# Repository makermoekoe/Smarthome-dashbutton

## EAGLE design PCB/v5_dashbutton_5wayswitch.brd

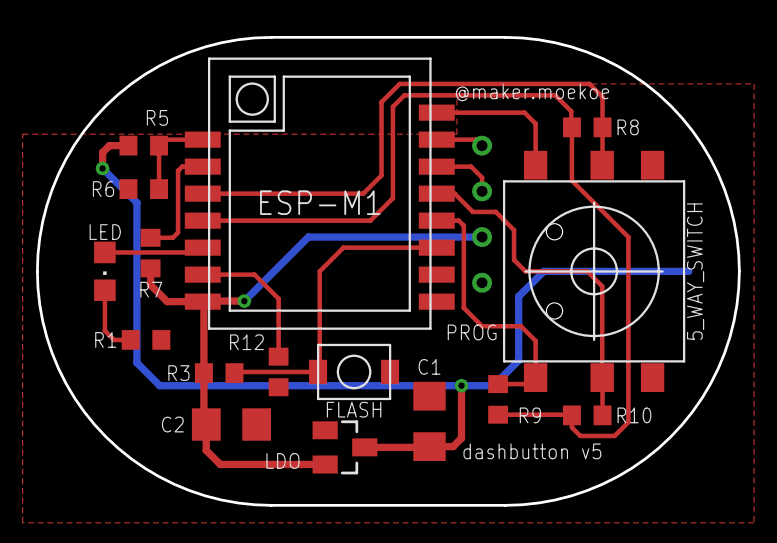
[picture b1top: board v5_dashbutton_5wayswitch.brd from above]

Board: 2 copper layers, 39.0 x 26.0 mm, 18 parts (1 on the bottom side), 16 nets.

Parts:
5_WAY_SWITCH: 5WAY_TACTILE_SWITCH
C1, C2: 1u; C1206
FLASH: 3X4_SMD_BUTTON; 3X4BUTTON
LDO: MCP1700; SOT23
LED: CHIPLED_0805
PROG: PROG_CON
R1: 1k; R0603
R3, R6, R7, R8, R9, R10, R12: 100k; R0603
R5: 330k; R0603
U$2: 2450_BATTERYHOLDER_SMD
U$3: ESP8285-M1

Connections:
4_5WAY_DOWN: 5_WAY_SWITCH.P6, R9.1, U$3.GPIO4
5_5WAY_RIGHT: 5_WAY_SWITCH.P5, R10.1, U$3.GPIO5
12_5WAY_HIGH: R8.1, R9.2, R10.2, U$3.GPIO12
14_5WAY_LEFT: 5_WAY_SWITCH.P2, R8.2, U$3.GPIO14
ADC: R5.2, R6.1, U$3.ADC
GND: 5_WAY_SWITCH.P1, C1.2, C2.2, FLASH.P$2, LDO.1, PROG.GND, R1.2, R6.2, R12.1, U$2.GND, U$3.GND
GPIO0_PROG: FLASH.P$1, R3.2, U$3.GPIO0
GPIO1: R12.2, U$3.GPIO15
GPIO13_LED: LED.A, U$3.GPIO13
unnamed: R7.2, U$3.EN
unnamed: LED.C, R1.1
RESET: 5_WAY_SWITCH.P3, U$3.RST
RXD: PROG.RXD, U$3.RXD
TXD: PROG.TXD, U$3.TXD
V33: C2.1, LDO.2, PROG.VCC, R3.1, R7.1, U$3.V33
VCC: C1.1, LDO.3, R5.1, U$2.VCC

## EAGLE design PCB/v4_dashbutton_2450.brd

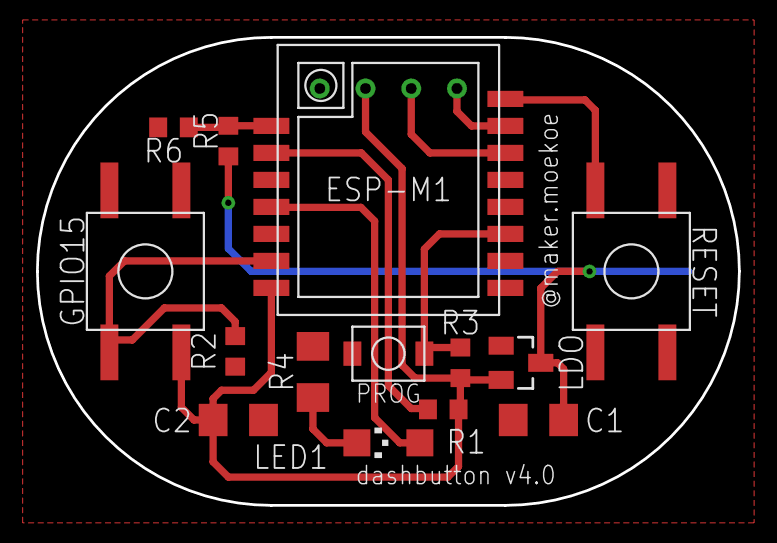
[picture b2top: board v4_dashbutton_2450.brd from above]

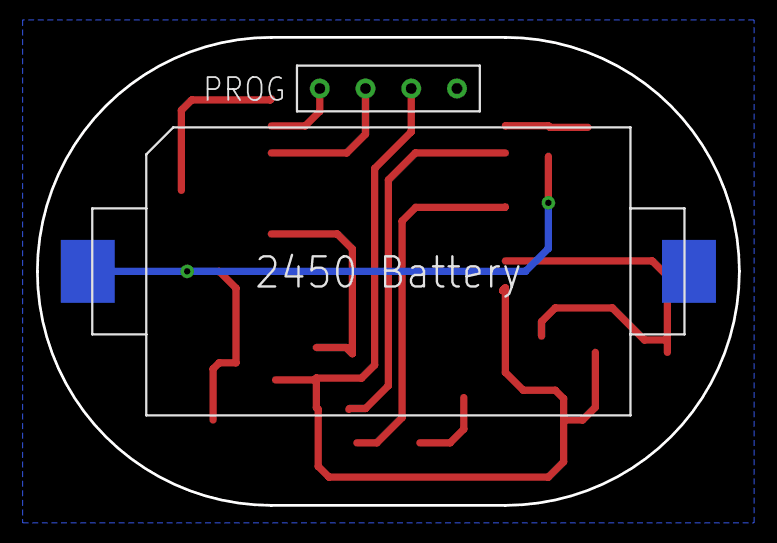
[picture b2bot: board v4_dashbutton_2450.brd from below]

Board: 2 copper layers, 39.0 x 26.0 mm, 16 parts (2 on the bottom side), 12 nets.

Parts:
C1, C2: 1u; C1206
GPIO15: 6X6BUTTON
LDO: MCP1700; SOT23
LED1: CHIPLED_1206
PROG: 3X4_SMD_BUTTON; 3X4BUTTON
R1, R2, R3: 10k; R0603
R4: R1206
R5: 330k; R0603
R6: 100k; R0603
RESET: 6X6BUTTON
U$2: 2450_BATTERYHOLDER_SMD
U$3: ESP8285-M1
U$6: PROG_CON

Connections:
ADC: R5.2, R6.1, U$3.ADC
GND: C1.2, C2.2, LDO.1, PROG.P$2, R2.1, R4.1, R6.2, RESET.P1, U$2.GND, U$3.GND, U$6.GND
GPIO0: PROG.P$1, R3.2, U$3.GPIO0
GPIO12: LED1.A, U$3.GPIO12
GPIO15: GPIO15.P4, R2.2, U$3.GPIO15
unnamed: LED1.C, R4.2
unnamed: R1.2, U$3.EN
RESET: RESET.P3, U$3.RST
RXD: U$3.RXD, U$6.RXD
TXD: U$3.TXD, U$6.TXD
V33: C2.1, GPIO15.P2, LDO.2, R1.1, R3.1, U$3.V33, U$6.VCC
VCC: C1.1, LDO.3, R5.1, U$2.VCC

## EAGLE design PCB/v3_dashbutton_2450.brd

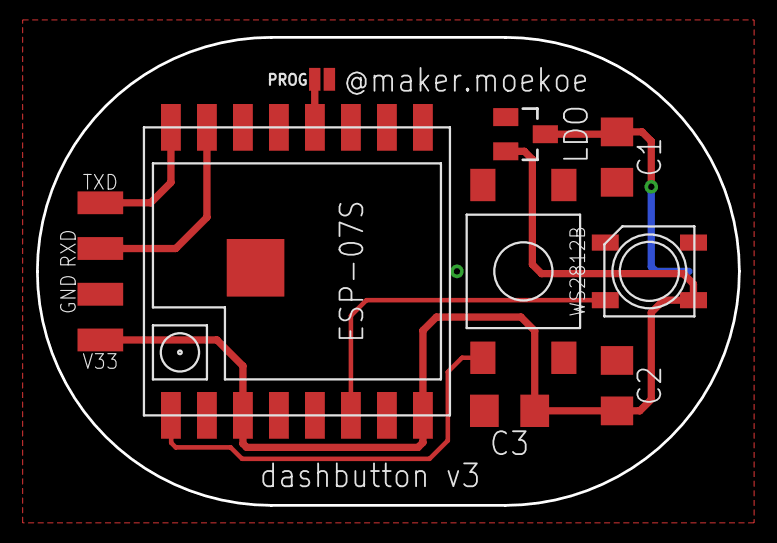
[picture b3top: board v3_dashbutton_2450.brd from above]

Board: 2 copper layers, 39.0 x 26.0 mm, 13 parts (1 on the bottom side), 8 nets.

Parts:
BUTTON: OMRON_B3FS_BUTTON; BUTTON_OMRON_B3FS
C1, C2: 1u; C1206
C3: 0,1u; C1206
GND: SMD1,27-2,54
LDO: MCP1700; SOT23
PROG: SMT-JUMPER_2_NO_NO-SILK
RXD: SMD1,27-2,54
TXD: SMD1,27-2,54
U$1: ESP8266-07S
U$2: 2450_BATTERYHOLDER_SMD
U$3: WS2812B
V33: SMD1,27-2,54

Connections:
GND: BUTTON.P$1, C1.2, C2.2, C3.2, GND.1, LDO.1, PROG.2, U$1.GND, U$1.GPIO15, U$2.GND, U$3.GND
GPIO0: PROG.1, U$1.GPIO0
GPIO12: U$1.GPIO12, U$3.DIN
RESET: BUTTON.P$4, U$1.RST
RXD: RXD.1, U$1.RXD
TXD: TXD.1, U$1.TXD
V33: C2.1, C3.1, LDO.2, U$1.EN, U$1.VCC, U$3.VCC, V33.1
VCC: C1.1, LDO.3, U$2.VCC

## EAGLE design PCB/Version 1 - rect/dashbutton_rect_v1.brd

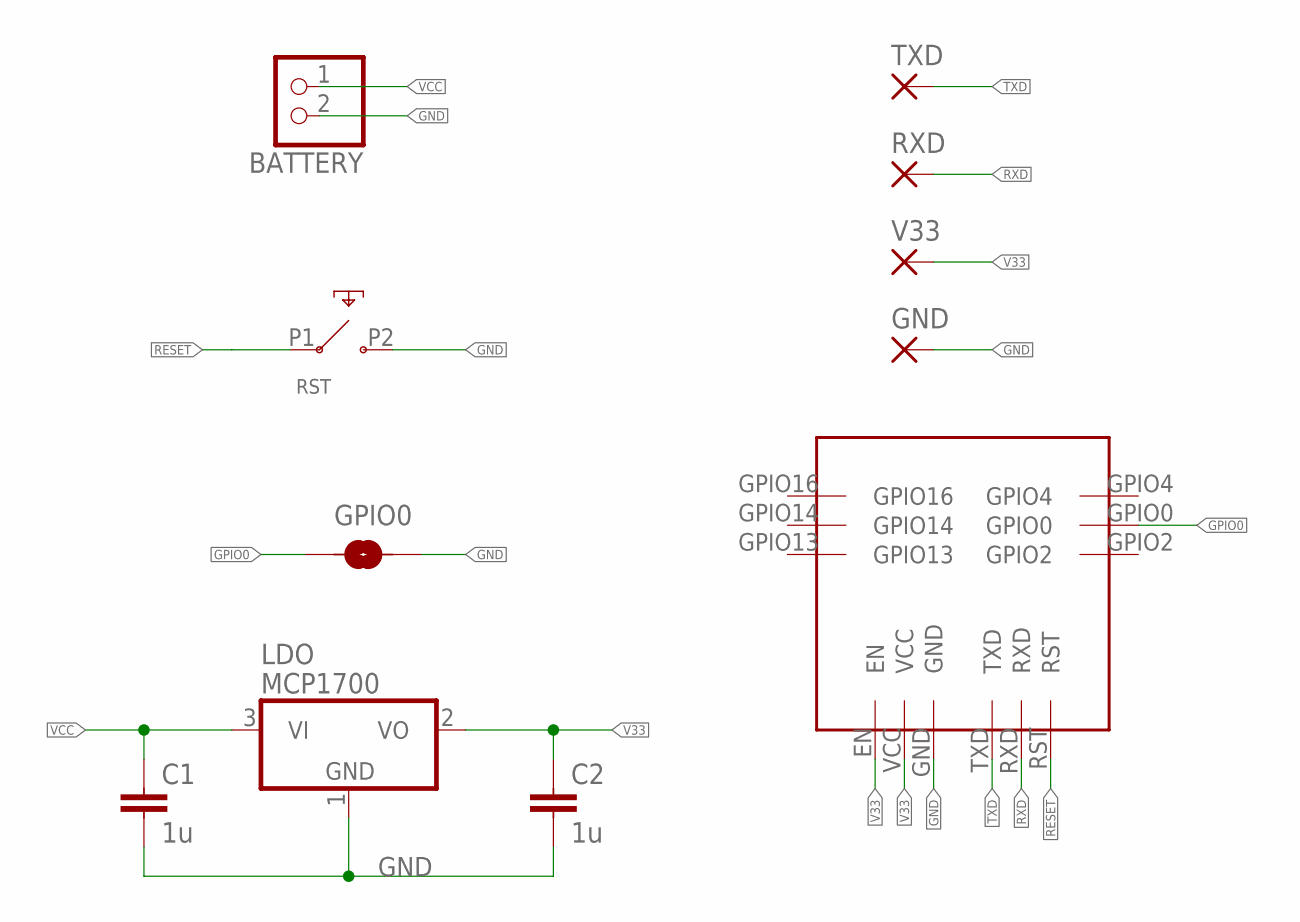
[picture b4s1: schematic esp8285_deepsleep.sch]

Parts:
BATTERY: JST_2PIN-SMT-RA; JST-PH-2-SMT-RA
C1, C2: 1u; C1206
GND: WIREPADSMD1,27-254; SMD1,27-2,54
GPIO0: JUMPER-SMT_2_NO_NO-SILK; SMT-JUMPER_2_NO_NO-SILK
LDO: MCP1700; SOT23
RST: 6X3_SMD_BUTTON_HALF; 6X3BUTTON
RXD: WIREPADSMD1,27-254; SMD1,27-2,54
TXD: WIREPADSMD1,27-254; SMD1,27-2,54
U$1: ESP8285-M3; ESP8285
V33: WIREPADSMD1,27-254; SMD1,27-2,54

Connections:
GND: BATTERY.2 (1), C1.2, C2.2, GND.1, GPIO0.2, LDO.1 (GND), RST.P2, U$1.GND
GPIO0: GPIO0.1, U$1.GPIO0
RESET: RST.P1, U$1.RST
RXD: RXD.1, U$1.RXD
TXD: TXD.1, U$1.TXD
V33: C2.1, LDO.2 (VO), U$1.EN, U$1.VCC, V33.1
VCC: BATTERY.1 (2), C1.1, LDO.3 (VI)

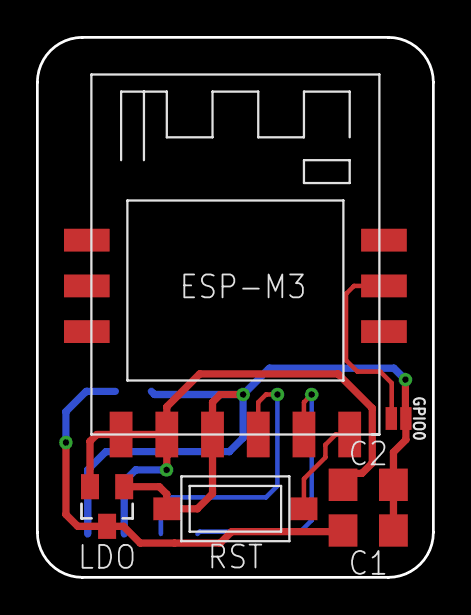
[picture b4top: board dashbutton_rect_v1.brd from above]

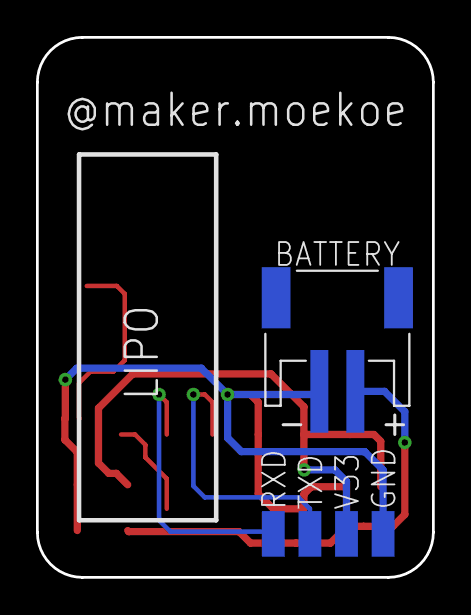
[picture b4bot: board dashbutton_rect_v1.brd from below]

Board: 2 copper layers, 22.0 x 30.0 mm, 11 parts (5 on the bottom side), 7 nets.

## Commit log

2018-12-04 dashbutton
2018-12-04 dashbutton text
2018-12-04 pictures
2018-12-04 alignment
2018-12-04 images
2018-12-05 added pcb files
2018-12-05 change order
2018-12-05 code
2018-12-09 pictures both
2018-12-09 resize pictures
2018-12-09 align
2018-12-09 pictures both versions
2018-12-09 resize
2018-12-09 added video
2018-12-09 hjds
2018-12-10 updated pictures
2018-12-25 added how to flash
2019-01-24 Added v3 and v4 pictures
2019-01-24 added 3d print case
2019-01-24 added 3d case
2019-02-11 added version 4
2019-02-19 added Arduino code for v4
2019-02-22 dbv4 case
2019-02-22 added dbv4 case
2019-02-27 version 4
2019-02-27 added Rssi measurements
2019-02-28 rssi measurements
2019-03-20 added dashbutton v5
2019-03-20 added version 5
2019-03-20 added code for version 5

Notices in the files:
parts and their libraries:
SparkFun-Jumpers: Licensing: Creative Commons ShareAlike 4.0 International - https://creativecommons.org/licenses/by-sa/4.0
